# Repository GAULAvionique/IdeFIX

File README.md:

<h1 align="center">Ordinateur de bord GAUL 2024-2025</h1>

<p align="left">

</p>

## 🌟 **Projet IdeFIX**

IdeFIX est une **balise de repérage embarquée** développée par le GAUL afin de faciliter la récupération et le suivi d’équipements après mission. Le système agit comme une plateforme compacte de télémétrie et de localisation capable de transmettre des informations essentielles en temps réel.

Le projet est conçu pour être :

* Léger et robuste
* Facilement intégrable dans une charge utile ou une fusée
* Optimisé pour une faible consommation énergétique
* Modulable selon les besoins de mission

L’objectif principal d’IdeFIX est d’assurer un repérage fiable des systèmes embarqués pendant les phases de récupération à courte distance.

---

## 📦 **Fonctionnalités Intégrées**

Le système se subdivise en deux cartes qui peuvent inclure plusieurs modules matériels et logiciels :

* **Communication Radio**

  Transmission des données vers une station sol pour le suivi et la récupération.

* **Microcontrôleur principal**

  Assure le traitement des données, la gestion des capteurs et les communications.

* **Gestion d’alimentation**

  Système optimisé pour maximiser l’autonomie et assurer la stabilité électrique.

* **Indicateurs de statut**

  LEDs, buzzer ou autres systèmes de rétroaction pour le diagnostic et le déboggage.

---

## 🛰 **Architecture du Projet**

Le dépôt contient l’ensemble des éléments nécessaires au développement de la balise :

* Firmware embarqué
* Drivers matériels
* Configuration des périphériques
* Documentation technique
* Outils de test et validation
* Scripts utilitaires

L’architecture logicielle vise à simplifier le développement et permettre une maintenance efficace du système.

---

## 📷 **Images du Projet**

Découvrez les différentes itérations et prototypes de la balise de repérage :

[Voir la Showcase](./Documentation/Showcase.md)

<div style="display: flex; justify-content: space-around;">

</div>

---

## 📚 **Documentation**

La documentation complète du projet est disponible dans le dossier `Documentation/`.

### Documentation matérielle

* [Composantes](./Documentation/Composantes.md)
* [Schémas](./Documentation/Schemas.md)
* [Assemblage](./Documentation/Assemblage.md)

### Documentation logicielle

* [Architecture logicielle](./Documentation/Architecture.md)
* [Drivers](./Documentation/Drivers.md)
* [Configuration](./Documentation/Configuration.md)
* [Prise en main](./Documentation/Logiciel.md)

### Développement

* [Guide de contribution](./Documentation/Contribution.md)
* [Tests et validation](./Documentation/Validation.md)

---

## ⚙ **Compilation et Déploiement**

Le projet est développé autour de l’écosystème STM32.

### Environnement recommandé

* STM32CubeIDE
* STM32CubeMX
* GCC ARM Toolchain

### Compilation

```bash
git clone https://github.com/GAULAvionique/IdeFIX.git
```

Ouvrir ensuite le projet dans STM32CubeIDE et compiler le firmware selon la configuration cible.

---

## 🛠 **Roadmap**

Fonctionnalités prévues et améliorations futures :

* Optimisation de la consommation énergétique
* Intégration LoRa longue portée
* Système de récupération automatique
* Interface de télémétrie améliorée
* Intégration de nouveaux capteurs
* Outils de visualisation des données

Consultez la [roadmap](./Documentation/Roadmap.md) pour plus de détails.

---

## 💡 **Liens Utiles**

* [STM32CubeIDE](https://www.st.com/en/development-tools/stm32cubeide.html)
* [Documentation STM32](https://www.st.com/)
* [Tutoriels STM32 — DeepBlueEmbedded](https://deepbluembedded.com/stm32-arm-programming-tutorials/)
* [GAUL](https://gaulspace.web.app/home)

---

## 👥 **Auteurs et Contributeurs**

* [@vides119](https://github.com/vides119)
* [@SamLol12](https://github.com/SamLol12)
* [Contributeurs GAUL](./Documentation/Participants.md)

---

🏠 Retour au la [page d'accueil](https://github.com/GAULAvionique2024-2025)

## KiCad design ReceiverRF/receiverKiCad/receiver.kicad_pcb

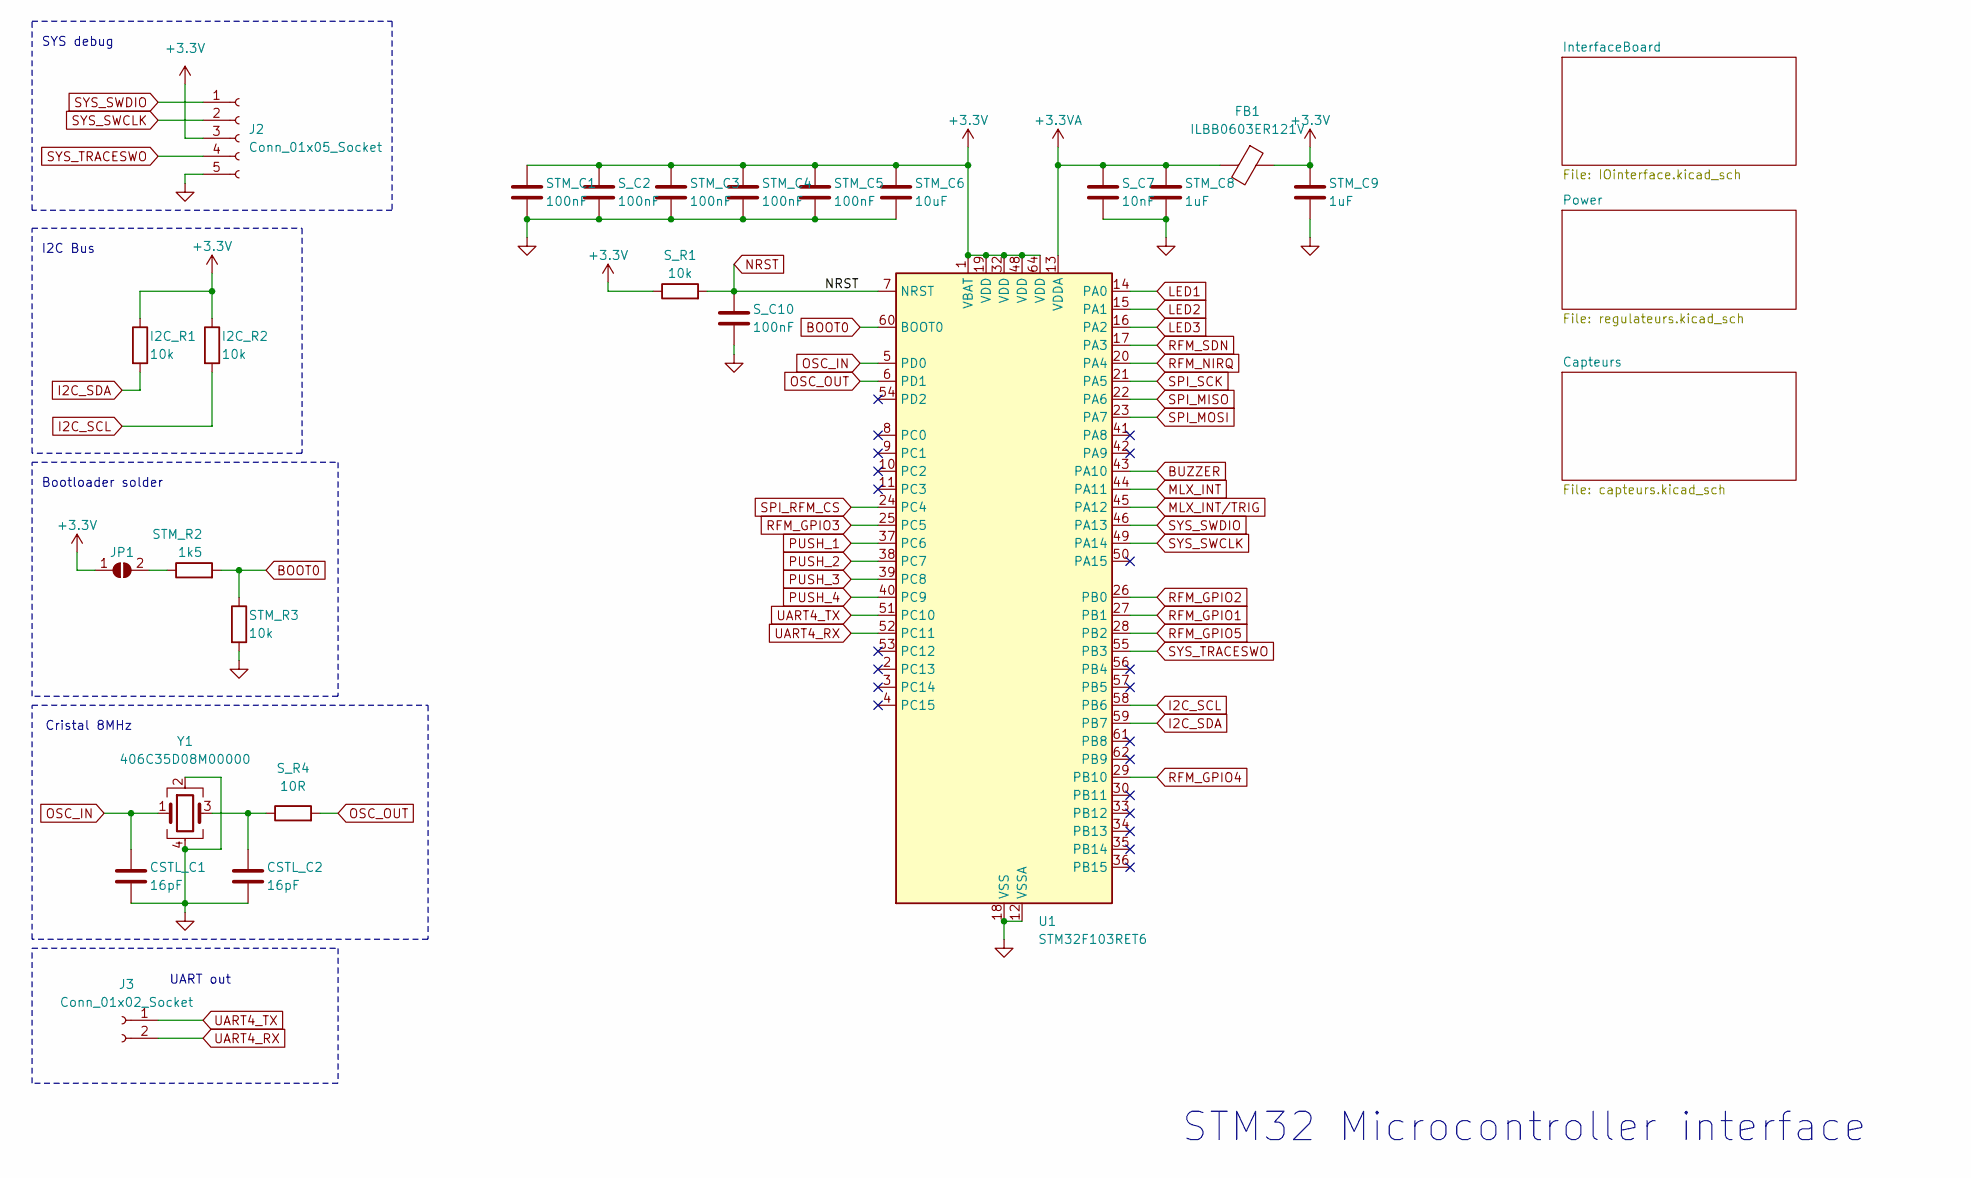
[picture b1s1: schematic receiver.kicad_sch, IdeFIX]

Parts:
CSTL_C1, CSTL_C2: 16pF; C_0603_1608Metric_Pad1.08x0.95mm_HandSolder; Digikey 399-CBR06C160F5GACCT-ND
FB1: ILBB0603ER121V; Ferrite_0603; Digikey 541-2290-1-ND
I2C_R1, I2C_R2: 10k; R_1206_3216Metric; Digikey 311-10.0KFRCT-ND
J2: Conn_01x05_Socket; PinHeader_1x05_P2.54mm_Vertical
J3: Conn_01x02_Socket; PinHeader_1x02_P2.54mm_Vertical
JP1: SolderJumper_2_Open; SolderJumper-2_P1.3mm_Open_TrianglePad1.0x1.5mm
STM_C1, STM_C3, STM_C4, STM_C5: 100nF; C_1206_3216Metric; Digikey 399-C1206C104K5RACTUCT-ND
STM_C6: 10uF; C_1206_3216Metric; Digikey 1276-1804-1-ND
STM_C8, STM_C9: 1uF; C_1206_3216Metric; Digikey 1276-1068-1-ND
STM_R2: 1k5; R_1206_3216Metric; Digikey 541-4184-1-ND
STM_R3: 10k; R_1206_3216Metric; Digikey 311-10.0KFRCT-ND
S_C2, S_C10: 100nF; C_1206_3216Metric; Digikey 399-C1206C104K5RACTUCT-ND
S_C7: 10nF; C_1206_3216Metric; Digikey 311-1174-1-ND
S_R1: 10k; R_1206_3216Metric; Digikey 311-10.0KFRCT-ND
S_R4: 10R; R_1206_3216Metric; Digikey RMCF1206FT10R0CT-ND
U1: STM32F103RET6; LQFP64-10x10mm; Digikey 497-6444-ND
Y1: 406C35D08M00000; Crystal; Digikey 110-406C35D08M00000CT-ND

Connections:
+3.3V: FB1.1, I2C_R1.1, I2C_R2.1, J2.3, JP1.1 (A), STM_C1.1, STM_C3.1, STM_C4.1, STM_C5.1, STM_C6.1, STM_C9.1, S_C2.1, S_R1.1, U1.1 (VBAT), U1.19 (VDD), U1.32 (VDD), U1.48 (VDD), U1.64 (VDD); also elsewhere on the board
+3.3VA: FB1.2, STM_C8.1, S_C7.1, U1.13 (VDDA)
BOOT0: STM_R2.2, STM_R3.1, U1.60 (BOOT0)
BUZZER: U1.43 (PA10); also elsewhere on the board
GND: CSTL_C1.2, CSTL_C2.2, J2.5, STM_C1.2, STM_C3.2, STM_C4.2, STM_C5.2, STM_C6.2, STM_C8.2, STM_C9.2, STM_R3.2, S_C2.2, S_C7.2, S_C10.2, U1.12 (VSSA), U1.18 (VSS), U1.31 (VSS), U1.47 (VSS), U1.63 (VSS), Y1.2, Y1.4; also elsewhere on the board
I2C_SCL: I2C_R2.2, U1.58 (PB6); also elsewhere on the board
I2C_SDA: I2C_R1.2, U1.59 (PB7); also elsewhere on the board
LED1: U1.14 (PA0); also elsewhere on the board
LED2: U1.15 (PA1); also elsewhere on the board
LED3: U1.16 (PA2); also elsewhere on the board
MLX_INT: U1.44 (PA11); also elsewhere on the board
MLX_INT/TRIG: U1.45 (PA12); also elsewhere on the board
NRST: S_C10.1, S_R1.2, U1.7 (NRST)
unnamed: CSTL_C2.1, S_R4.1, Y1.3
unnamed: JP1.2 (B), STM_R2.1
OSC_IN: CSTL_C1.1, U1.5 (PD0), Y1.1
OSC_OUT: S_R4.2, U1.6 (PD1)
PUSH_1: U1.37 (PC6); also elsewhere on the board
PUSH_2: U1.38 (PC7); also elsewhere on the board
PUSH_3: U1.39 (PC8); also elsewhere on the board
PUSH_4: U1.40 (PC9); also elsewhere on the board
RFM_GPIO1: U1.27 (PB1); also elsewhere on the board
RFM_GPIO2: U1.26 (PB0); also elsewhere on the board
RFM_GPIO3: U1.25 (PC5); also elsewhere on the board
RFM_GPIO4: U1.29 (PB10); also elsewhere on the board
RFM_GPIO5: U1.28 (PB2); also elsewhere on the board
RFM_NIRQ: U1.20 (PA4); also elsewhere on the board
RFM_SDN: U1.17 (PA3); also elsewhere on the board
SPI_MISO: U1.22 (PA6); also elsewhere on the board
SPI_MOSI: U1.23 (PA7); also elsewhere on the board
SPI_RFM_CS: U1.24 (PC4); also elsewhere on the board
SPI_SCK: U1.21 (PA5); also elsewhere on the board
SYS_SWCLK: J2.2, U1.49 (PA14)
SYS_SWDIO: J2.1, U1.46 (PA13)
SYS_TRACESWO: J2.4, U1.55 (PB3)
UART4_RX: J3.2, U1.52 (PC11)
UART4_TX: J3.1, U1.51 (PC10)

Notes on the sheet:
I2C Bus
STM32 Microcontroller interface
Cristal 8MHz
Bootloader solder
SYS debug
UART out

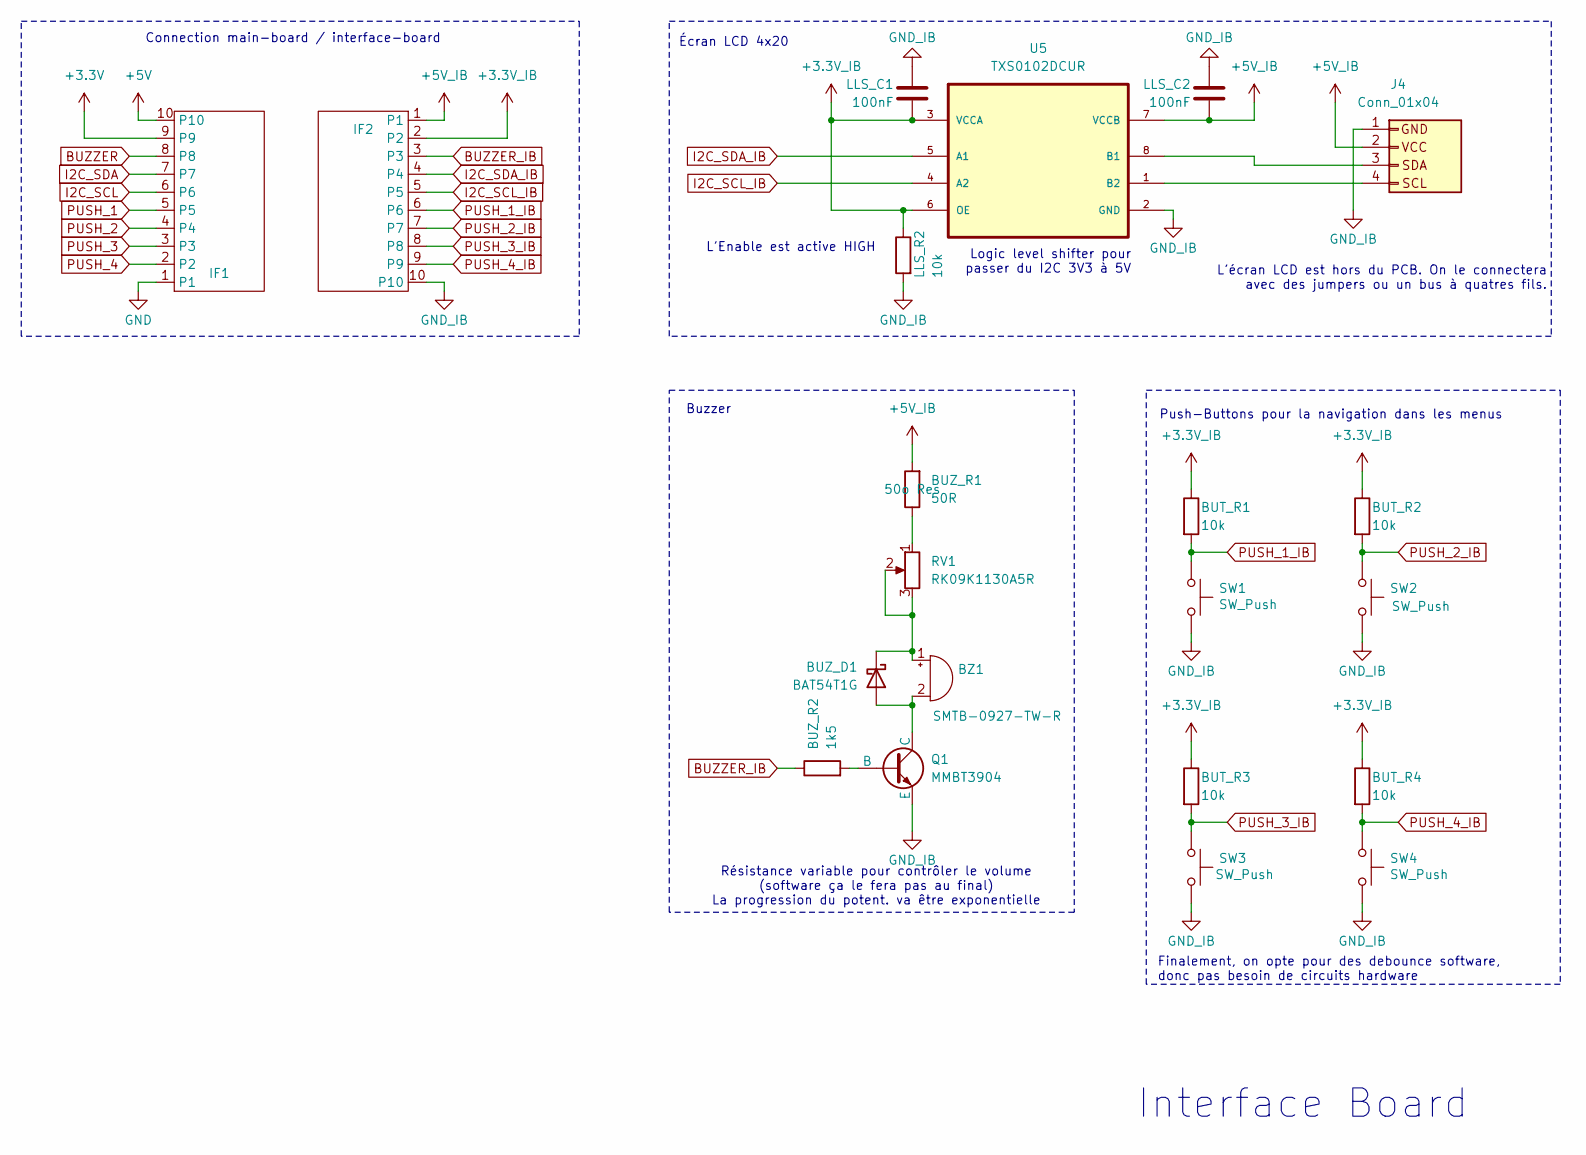
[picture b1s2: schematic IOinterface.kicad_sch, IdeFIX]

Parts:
BUT_R1, BUT_R2, BUT_R3, BUT_R4: 10k; R_1206_3216Metric; Digikey 311-10.0KFRCT-ND
BUZ_D1: BAT54T1G; D_SOD-123; Digikey BAT54T1GOSCT-ND
BUZ_R1: 50R; R_1206_3216Metric; Digikey 541-TNPW120650R0BEENCT-ND
BUZ_R2: 1k5; R_1206_3216Metric; Digikey 541-4184-1-ND
BZ1: SMTB-0927-TW-R; Buzzer_D14mm_H7mm_P10mm; Digikey 668-SMTB-0927-TW-RCT-ND
IF1, IF2: CONN10_530481010_MOL; Digikey WM1750-ND
J4: Conn_01x04; PinHeader_1x04_P2.54mm_Vertical
LLS_C1, LLS_C2: 100nF; C_1206_3216Metric; Digikey 399-C1206C104K5RACTUCT-ND
LLS_R2: 10k; R_1206_3216Metric; Digikey 311-10.0KFRCT-ND
Q1: MMBT3904; SOT-23; Digikey MMBT3904LT1GOSCT-ND
RV1: RK09K1130A5R; Potentiometer_Alps_RK09K_Single_Vertical; Digikey 4809-RK09K1130A5R-ND
SW1, SW2, SW3, SW4: SW_Push; SW_PUSH_6mm_H4.3mm; Digikey EG1862-ND
U5: TXS0102DCUR; SOP50P310X90-8N; Digikey 296-21931-2-ND

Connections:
+3.3V: IF1.9; also elsewhere on the board
+3.3V_IB: BUT_R1.1, BUT_R2.1, BUT_R3.1, BUT_R4.1, IF2.2, LLS_C1.2, LLS_R2.1, U5.3 (VCCA), U5.6 (OE)
+5V: IF1.10; also elsewhere on the board
+5V_IB: BUZ_R1.2, IF2.1, J4.2 (VCC), LLS_C2.2, U5.7 (VCCB)
BUZZER: IF1.8; also elsewhere on the board
BUZZER_IB: BUZ_R2.1, IF2.3
GND: IF1.1; also elsewhere on the board
GND_IB: IF2.10, J4.1 (GND), LLS_C1.1, LLS_C2.1, LLS_R2.2, Q1.3 (E), SW1.2, SW2.2, SW3.2, SW4.2, U5.2 (GND)
I2C_SCL: IF1.6; also elsewhere on the board
I2C_SCL_IB: IF2.5, U5.4 (A2)
I2C_SDA: IF1.7; also elsewhere on the board
I2C_SDA_IB: IF2.4, U5.5 (A1)
unnamed: BUZ_D1.2 (A), BZ1.2 (+), Q1.1 (C)
unnamed: BUZ_D1.1 (K), BZ1.1 (-), RV1.2, RV1.3
unnamed: BUZ_R1.1, RV1.1
unnamed: J4.4 (SCL), U5.1 (B2)
unnamed: J4.3 (SDA), U5.8 (B1)
unnamed: BUZ_R2.2, Q1.2 (B)
PUSH_1: IF1.5; also elsewhere on the board
PUSH_1_IB: BUT_R1.2, IF2.6, SW1.1
PUSH_2: IF1.4; also elsewhere on the board
PUSH_2_IB: BUT_R2.2, IF2.7, SW2.1
PUSH_3: IF1.3; also elsewhere on the board
PUSH_3_IB: BUT_R3.2, IF2.8, SW3.1
PUSH_4: IF1.2; also elsewhere on the board
PUSH_4_IB: BUT_R4.2, IF2.9, SW4.1

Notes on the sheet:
Logic level shifter pour passer du I2C 3V3 à 5V
Interface Board
Connection main-board / interface-board
L'écran LCD est hors du PCB. On le connectera avec des jumpers ou un bus à quatres fils.
Finalement, on opte pour des debounce software, donc pas besoin de circuits hardware
Écran LCD 4x20
Résistance variable pour contrôler le volume (software ça le fera pas au final) La progression du potent. va être exponentielle
Buzzer
Push-Buttons pour la navigation dans les menus
L'Enable est active HIGH

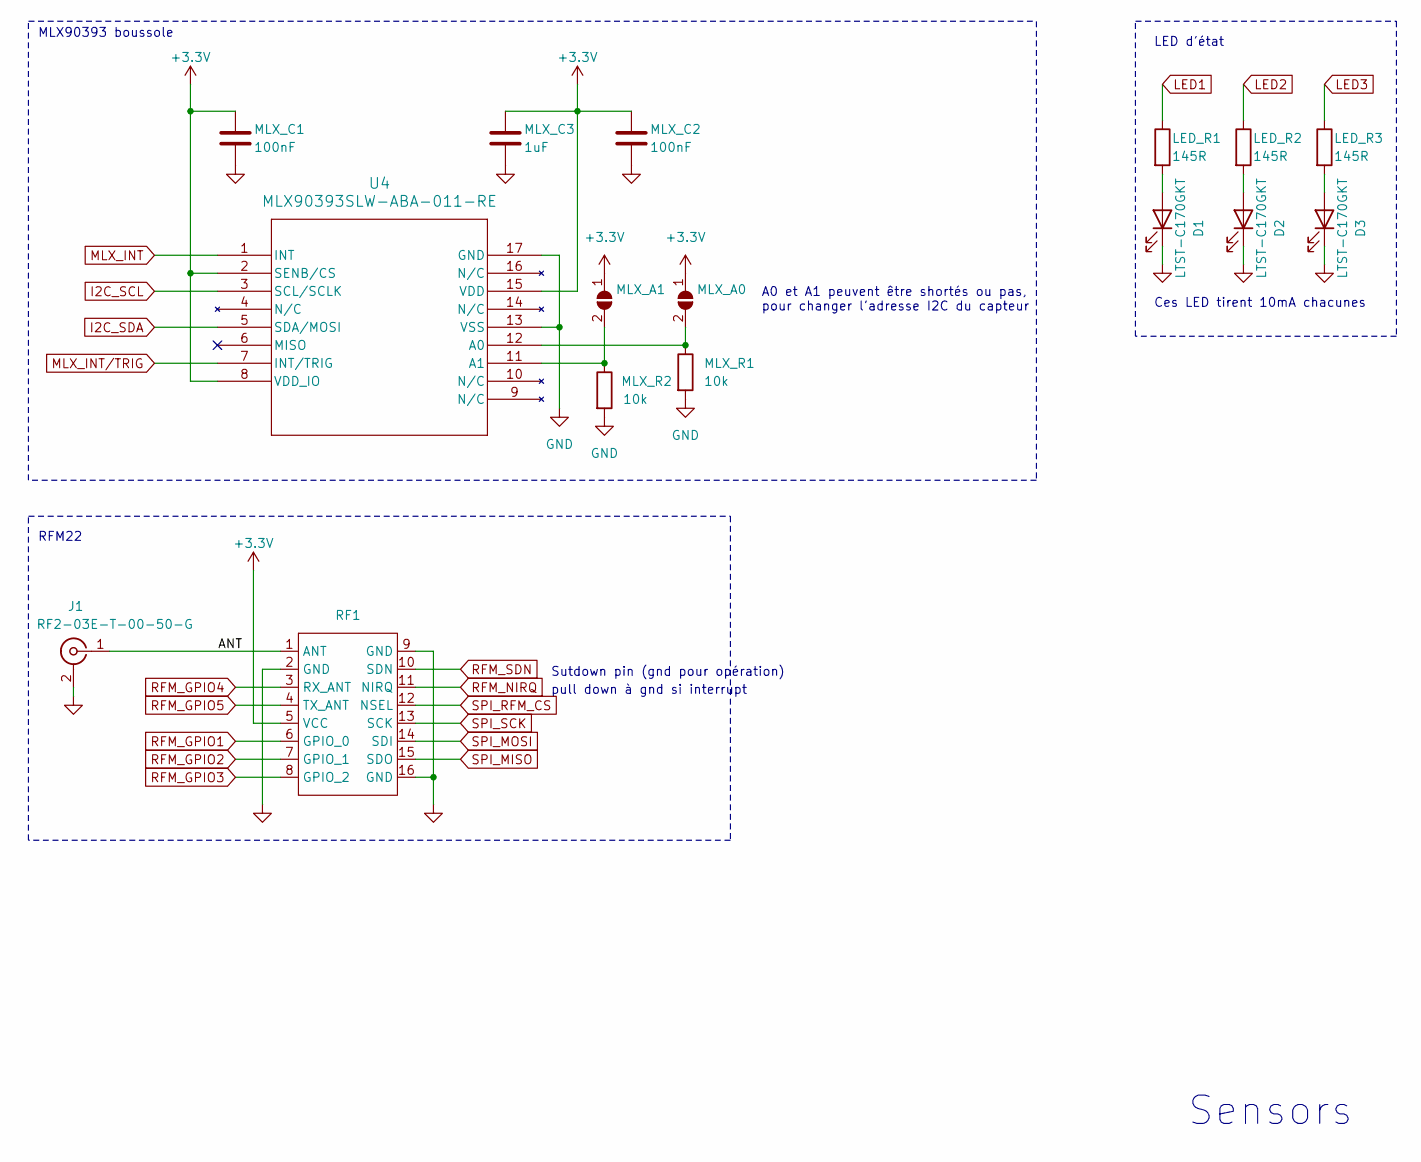
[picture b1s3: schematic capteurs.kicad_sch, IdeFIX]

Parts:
D1, D2, D3: LTST-C170GKT; Digikey 160-1414-1-ND
J1: RF2-03E-T-00-50-G; SMA_90deg; Digikey 2057-RF2-03E-T-00-50-G-ND
LED_R1, LED_R2, LED_R3: 145R; R_1206_3216Metric; Digikey 2019-RN73H2BTTD1450F100CT-ND
MLX_A0, MLX_A1: jumper; SolderJumper-2_P1.3mm_Open_TrianglePad1.0x1.5mm
MLX_C1, MLX_C2: 100nF; C_1206_3216Metric; Digikey 399-C1206C104K5RACTUCT-ND
MLX_C3: 1uF; C_1206_3216Metric; Digikey 1276-1068-1-ND
MLX_R1, MLX_R2: 10k; R_1206_3216Metric; Digikey 311-10.0KFRCT-ND
RF1: RFM22B; RFM22b-S2_TH
U4: MLX90393SLW-ABA-011-RE; QFN-16_MLX90393_MEL-L; Digikey MLX90393SLW-ABA-011-RECT-ND

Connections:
+3.3V: MLX_A0.1 (A), MLX_A1.1 (A), MLX_C1.1, MLX_C2.1, MLX_C3.1, RF1.5 (VCC), U4.2 (SENB/CS), U4.8 (VDD_IO), U4.15 (VDD); also elsewhere on the board
/Capteurs/ANT: J1.1 (In), RF1.1 (ANT)
GND: D1.1 (K), D2.1 (K), D3.1 (K), J1.2 (Ext), MLX_C1.2, MLX_C2.2, MLX_C3.2, MLX_R1.2, MLX_R2.2, RF1.2 (GND), RF1.9 (GND), RF1.16 (GND), U4.13 (VSS), U4.17 (GND); also elsewhere on the board
I2C_SCL: U4.3 (SCL/SCLK); also elsewhere on the board
I2C_SDA: U4.5 (SDA/MOSI); also elsewhere on the board
LED1: LED_R1.1; also elsewhere on the board
LED2: LED_R2.1; also elsewhere on the board
LED3: LED_R3.1; also elsewhere on the board
MLX_INT: U4.1 (INT); also elsewhere on the board
MLX_INT/TRIG: U4.7 (INT/TRIG); also elsewhere on the board
unnamed: D1.2 (A), LED_R1.2
unnamed: D2.2 (A), LED_R2.2
unnamed: D3.2 (A), LED_R3.2
unnamed: MLX_A0.2 (B), MLX_R1.1, U4.12 (A0)
unnamed: MLX_A1.2 (B), MLX_R2.1, U4.11 (A1)
RFM_GPIO1: RF1.6 (GPIO_0); also elsewhere on the board
RFM_GPIO2: RF1.7 (GPIO_1); also elsewhere on the board
RFM_GPIO3: RF1.8 (GPIO_2); also elsewhere on the board
RFM_GPIO4: RF1.3 (RX_ANT); also elsewhere on the board
RFM_GPIO5: RF1.4 (TX_ANT); also elsewhere on the board
RFM_NIRQ: RF1.11 (NIRQ); also elsewhere on the board
RFM_SDN: RF1.10 (SDN); also elsewhere on the board
SPI_MISO: RF1.15 (SDO); also elsewhere on the board
SPI_MOSI: RF1.14 (SDI); also elsewhere on the board
SPI_RFM_CS: RF1.12 (NSEL); also elsewhere on the board
SPI_SCK: RF1.13 (SCK); also elsewhere on the board

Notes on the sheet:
Ces LED tirent 10mA chacunes
pull down à gnd si interrupt
Sutdown pin (gnd pour opération)
MLX90393 boussole
LED d'état
Sensors
RFM22
A0 et A1 peuvent être shortés ou pas, pour changer l'adresse I2C du capteur

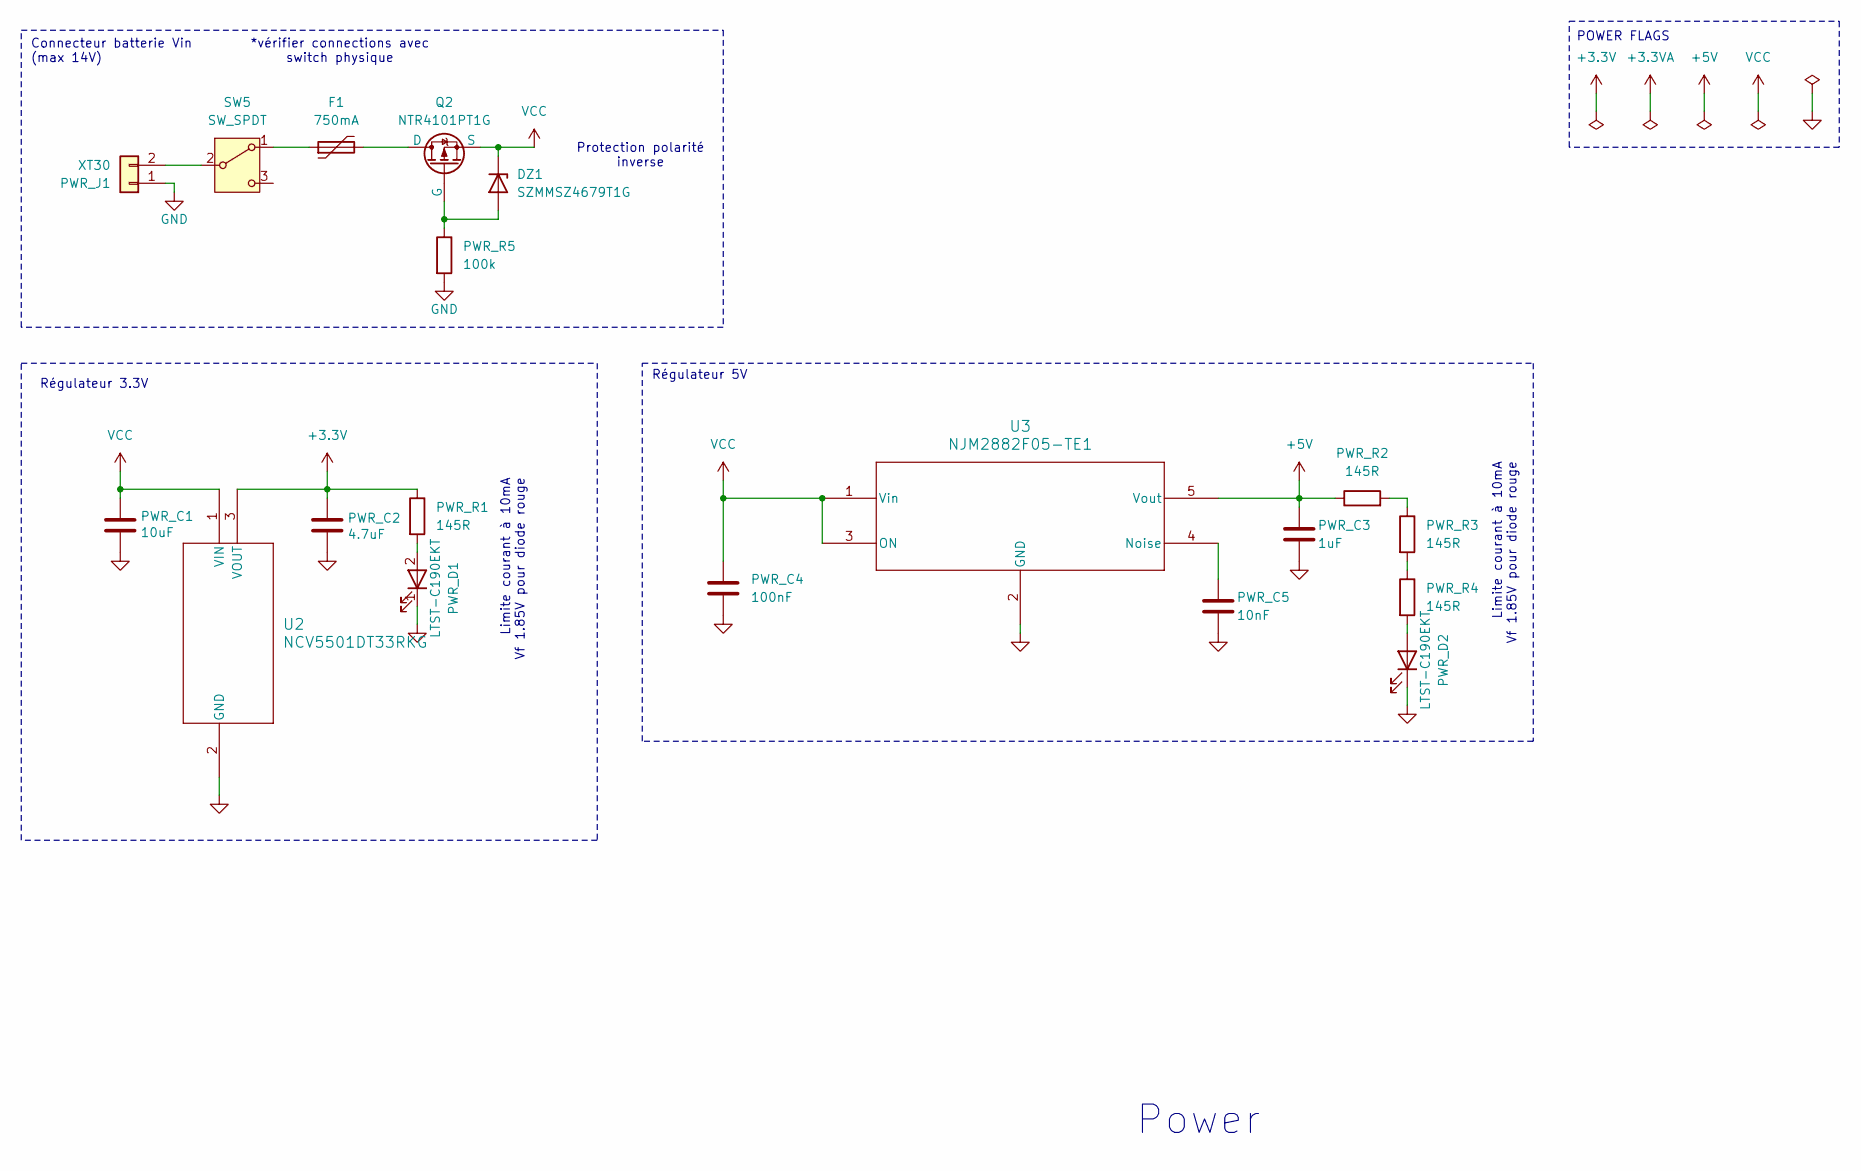
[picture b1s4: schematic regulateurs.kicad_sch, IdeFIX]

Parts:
DZ1: SZMMSZ4679T1G; D_SOD-123; Digikey SZMMSZ4679T1GOSCT-ND
F1: 750mA; Polyfuse; Digikey 118-MF-NSMF075/13X-2CT-ND
PWR_C1: 10uF; C_1206_3216Metric; Digikey 1276-1804-1-ND
PWR_C2: 4.7uF; C_1206_3216Metric; Digikey 1276-3182-1-ND
PWR_C3: 1uF; C_1206_3216Metric; Digikey 1276-1068-1-ND
PWR_C4: 100nF; C_1206_3216Metric; Digikey 399-C1206C104K5RACTUCT-ND
PWR_C5: 10nF; C_1206_3216Metric; Digikey 311-1174-1-ND
PWR_D1, PWR_D2: LTST-C190EKT; Digikey 516-1422-1-ND
PWR_J1: XT30; AMASS_XT30U-M_1x02_P5.0mm_Vertical; Digikey 1568-10474-ND
PWR_R1, PWR_R2, PWR_R3, PWR_R4: 145R; R_1206_3216Metric; Digikey 2019-RN73H2BTTD1450F100CT-ND
PWR_R5: 100k; R_1206_3216Metric; Digikey 541-100KUCT-ND
Q2: NTR4101PT1G; SOT-23; Digikey NTR4101PT1GOSCT-ND
SW5: SW_SPDT; CS12ANW03_NKK; Digikey 360-2131-ND
U2: NCV5501DT33RKG; DPAK-3_ONS-M; Digikey NCV5501DT33RKGOSCT-ND
U3: NJM2882F05-TE1; SOT-23-5; Digikey 2129-NJM2882F05-TE1CT-ND

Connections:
+3.3V: PWR_C2.1, PWR_R1.1, U2.3 (VOUT); also elsewhere on the board
+5V: PWR_C3.1, PWR_R2.1, U3.5 (Vout); also elsewhere on the board
GND: PWR_C1.2, PWR_C2.2, PWR_C3.2, PWR_C4.2, PWR_C5.2, PWR_D1.1 (K), PWR_D2.1 (K), PWR_J1.1, PWR_R5.2, U2.2 (GND), U3.2 (GND); also elsewhere on the board
unnamed: DZ1.2 (A), PWR_R5.1, Q2.2 (G)
unnamed: PWR_D1.2 (A), PWR_R1.2
unnamed: PWR_D2.2 (A), PWR_R4.2
unnamed: PWR_J1.2, SW5.2 (B)
unnamed: PWR_R2.2, PWR_R3.1
unnamed: PWR_R3.2, PWR_R4.1
unnamed: F1.2, Q2.1 (D)
unnamed: F1.1, SW5.1 (A)
unnamed: PWR_C5.1, U3.4 (Noise)
VCC: DZ1.1 (K), PWR_C1.1, PWR_C4.1, Q2.3 (S), U2.1 (VIN), U3.1 (Vin), U3.3 (ON)

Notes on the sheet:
Limite courant à 10mA Vf 1.85V pour diode rouge
Power
Protection polarité inverse
Connecteur batterie Vin (max 14V)
POWER FLAGS
Régulateur 5V
*vérifier connections avec switch physique
Régulateur 3.3V

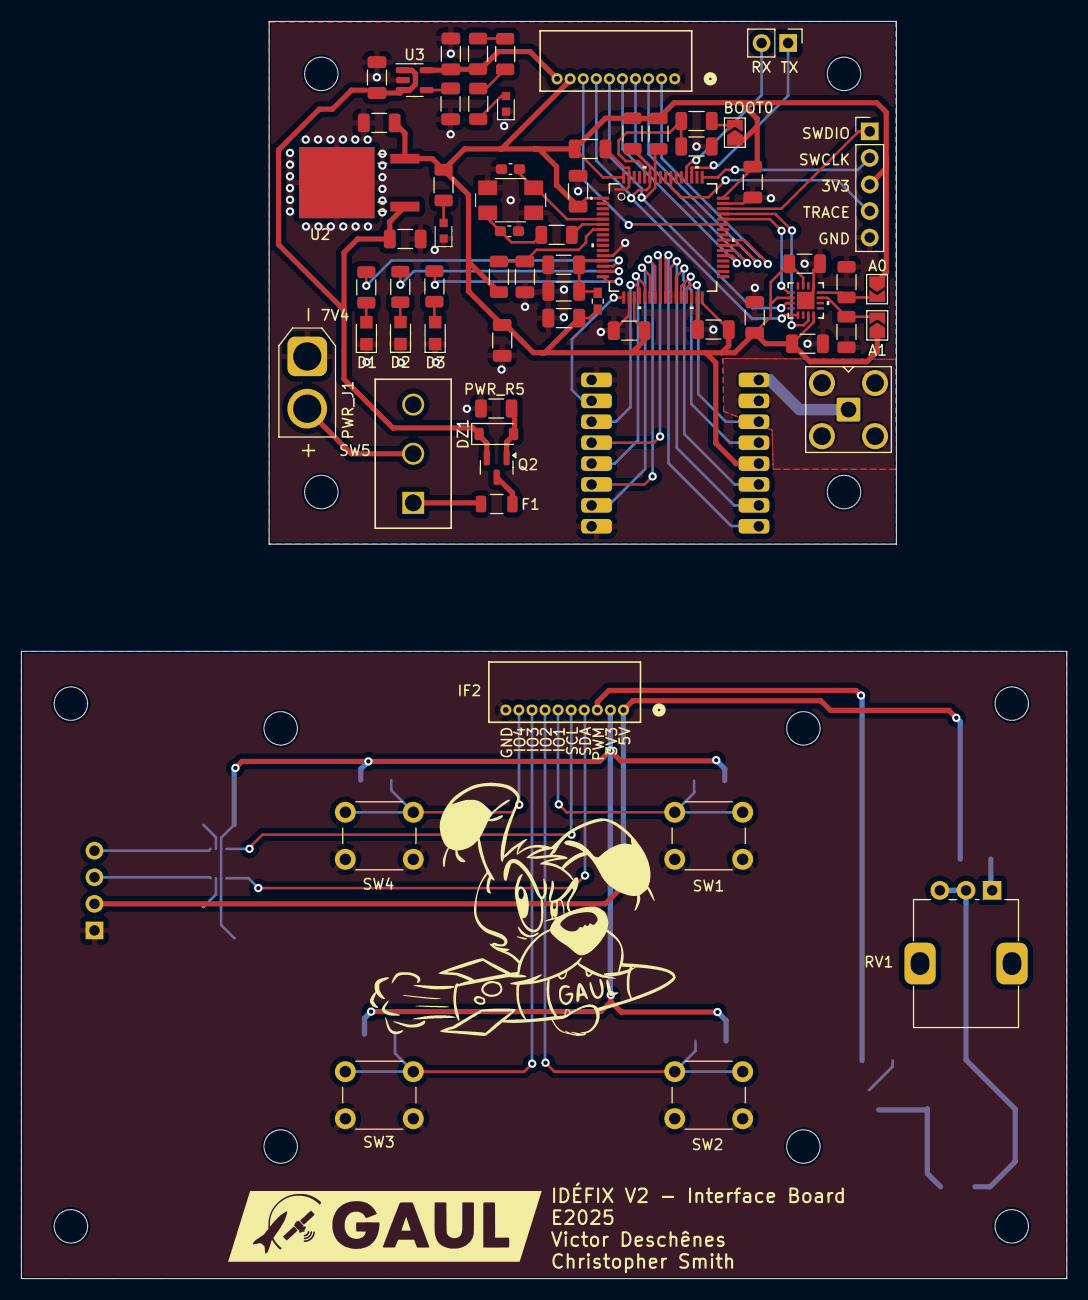
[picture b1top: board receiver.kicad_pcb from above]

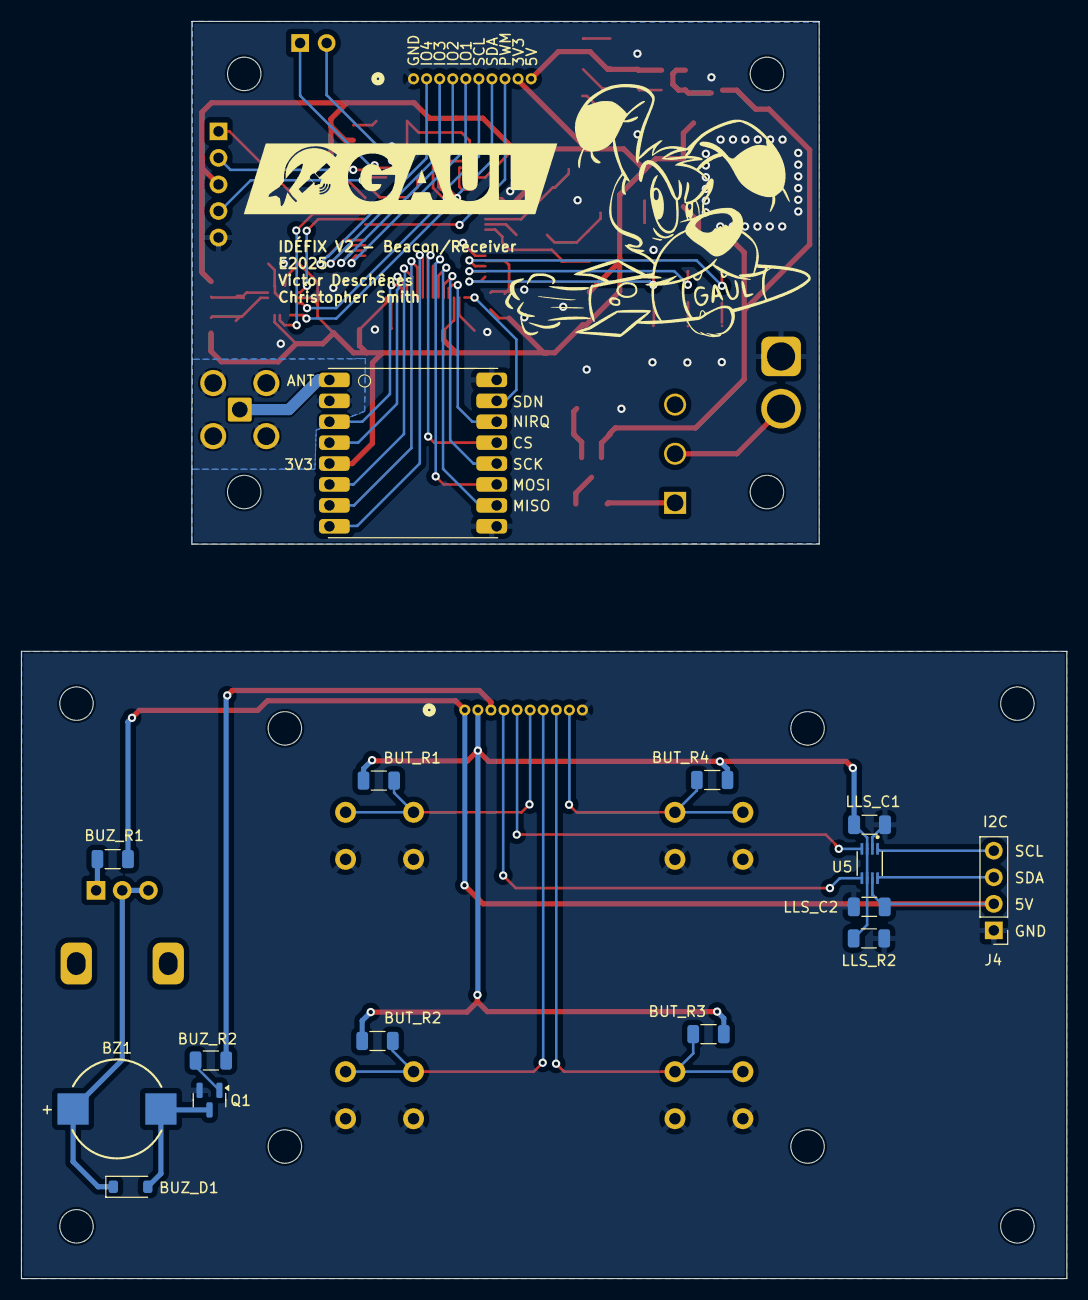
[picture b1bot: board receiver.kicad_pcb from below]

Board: 2 copper layers, 100.0 x 120.3 mm, 83 parts (15 on the bottom side), 70 nets.

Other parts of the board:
HOLES1, HOLES2: Mounting_holes
HOLES3: Mounting_holes_big

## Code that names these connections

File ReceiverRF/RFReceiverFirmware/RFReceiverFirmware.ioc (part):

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Mcu.Name=STM32F103R(C-D-E)Tx
Mcu.Package=LQFP64
Mcu.UserName=STM32F103RETx
PA0-WKUP.GPIOParameters=GPIO_Label
PA0-WKUP.GPIO_Label=LED1
PA0-WKUP.Signal=GPIO_Output
PA1.GPIOParameters=GPIO_Label
PA1.GPIO_Label=LED2
PA1.Signal=GPIO_Output
PA10.Signal=GPIO_Output
PA11.GPIOParameters=GPIO_Label
PA11.GPIO_Label=MLX_INT_TRIG
PA11.Signal=GPIO_Input
PA12.GPIOParameters=GPIO_Label
PA12.GPIO_Label=MLX_INT
PA12.Signal=GPIO_Input
PA13.Mode=Trace_Asynchronous_SW
PA13.Signal=SYS_JTMS-SWDIO
PA14.Mode=Trace_Asynchronous_SW
PA14.Signal=SYS_JTCK-SWCLK
PA2.GPIOParameters=GPIO_Label
PA2.GPIO_Label=LED3
PA2.Signal=GPIO_Output
PA3.GPIOParameters=GPIO_Label
PA3.GPIO_Label=RFM_SDN
PA3.Signal=GPIO_Output
PA4.GPIOParameters=GPIO_Label
PA4.GPIO_Label=RFM_IRQ
PA4.Signal=GPIO_Output
PA5.Mode=Full_Duplex_Master
PA5.Signal=SPI1_SCK
PA6.Mode=Full_Duplex_Master
PA6.Signal=SPI1_MISO
PA7.Mode=Full_Duplex_Master
PA7.Signal=SPI1_MOSI
PA8.Signal=S_TIM1_CH1
PB0.GPIOParameters=GPIO_Label
PB0.GPIO_Label=RFM_GPIO2
PB0.Signal=GPIO_Output
PB1.GPIOParameters=GPIO_Label
PB1.GPIO_Label=RFM_GPIO1
PB1.Signal=GPIO_Output
PB10.GPIOParameters=GPIO_Label
PB10.GPIO_Label=RFM_GPIO4
PB10.Signal=GPIO_Output
PB2.GPIOParameters=GPIO_Label
PB2.GPIO_Label=RFM_GPIO5
PB2.Signal=GPIO_Output
PB3.Mode=Trace_Asynchronous_SW
PB3.Signal=SYS_JTDO-TRACESWO
PB6.Mode=I2C
PB6.Signal=I2C1_SCL
PB7.Mode=I2C
PB7.Signal=I2C1_SDA
PC10.Mode=Asynchronous
PC10.Signal=UART4_TX
PC11.Mode=Asynchronous
PC11.Signal=UART4_RX
PC4.GPIOParameters=GPIO_Label
PC4.GPIO_Label=RFM_CS
PC4.Signal=GPIO_Output
PC5.GPIOParameters=GPIO_Label
PC5.GPIO_Label=RFM_GPIO3
PC5.Signal=GPIO_Output
PC6.GPIOParameters=GPIO_Label
PC6.GPIO_Label=GPIO1
PC6.Signal=GPIO_Input
PC7.GPIOParameters=GPIO_Label
PC7.GPIO_Label=GPIO2
PC7.Signal=GPIO_Input
PC8.GPIOParameters=GPIO_Label
PC8.GPIO_Label=GPIO3
PC8.Signal=GPIO_Input
PC9.GPIOParameters=GPIO_Label
PC9.GPIO_Label=GPIO4
PC9.Signal=GPIO_Input
RCC.SYSCLKFreq_VALUE=64000000
RCC.SYSCLKSource=RCC_SYSCLKSOURCE_PLLCLK
board=custom

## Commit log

2025-03-03 correction mineure, logo Idefix, commande PCBWAY
2025-03-03 changement cristal
2025-03-07 changement vers footprint 1206
2025-03-07 changement BOM et choix nouvelles pièces 1206
2025-03-08 Ajout date, nom et version
2025-03-08 Auto stash before checking out "origin/ODB"
    nom et commande
2025-04-11 firmware oscillateur interne :(
2025-04-15 firmware dossiers gaul drivers
2025-04-15 SPI rfm fonctionnel
2025-05-17 tx rfm fonctionnel
2025-05-27 librairie RFM22 fonctionnelle
2025-06-01 lcd working, buzzer marche avec fix temporaire, IO fonctionnels
2025-06-03 receiver fonctionnel, manque parsing du GPS
2025-07-09 ideFIX v2 fix schematic, layout
2025-07-10 revision schematic before tracing
2025-07-11 Final layout and routing
2025-07-14 finished silkscreen and added logos
2025-07-15 fix zener diode footprint, thermal relief on SMA conn, more work on silkscreen
2025-07-22 3.2mm holes, XT30 connector, add polyfuse, minor fixes
2025-08-04 Refactor timer handling and add TRANSMIT/RECEIVE definition macros
2025-08-10 working receiver and transmitter firmware for new hardware, added frequency display and strenght bar
2025-10-31 added .gitignore file
2025-11-04 mlx90393 header file
2025-11-07 début implementation write/receive i2c pour capteur MLX90393
2025-11-12 fix: .gitignore
2026-05-18 (ajout) ajout de la fonction de modification de fréquence + du code d'identification
2026-05-27 (fork) insertion de ce qui étais dans mon fork.
2026-05-28 Revise README for IdeFIX project details (draft)
